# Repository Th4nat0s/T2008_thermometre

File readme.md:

Attiny84 Thermometer
=====================

Push code to attiny84
--------------------------------

### Attiny84
SPI Through BusPirate 
arduino framework 

Tips
----
`pio run` process/build project from the current directory  
`pio run -t upload` - upload firmware to a target  
`pio run -t clean` - clean project (remove compiled files)  
`pio run -t upload -e uno` upload only for arduino uno

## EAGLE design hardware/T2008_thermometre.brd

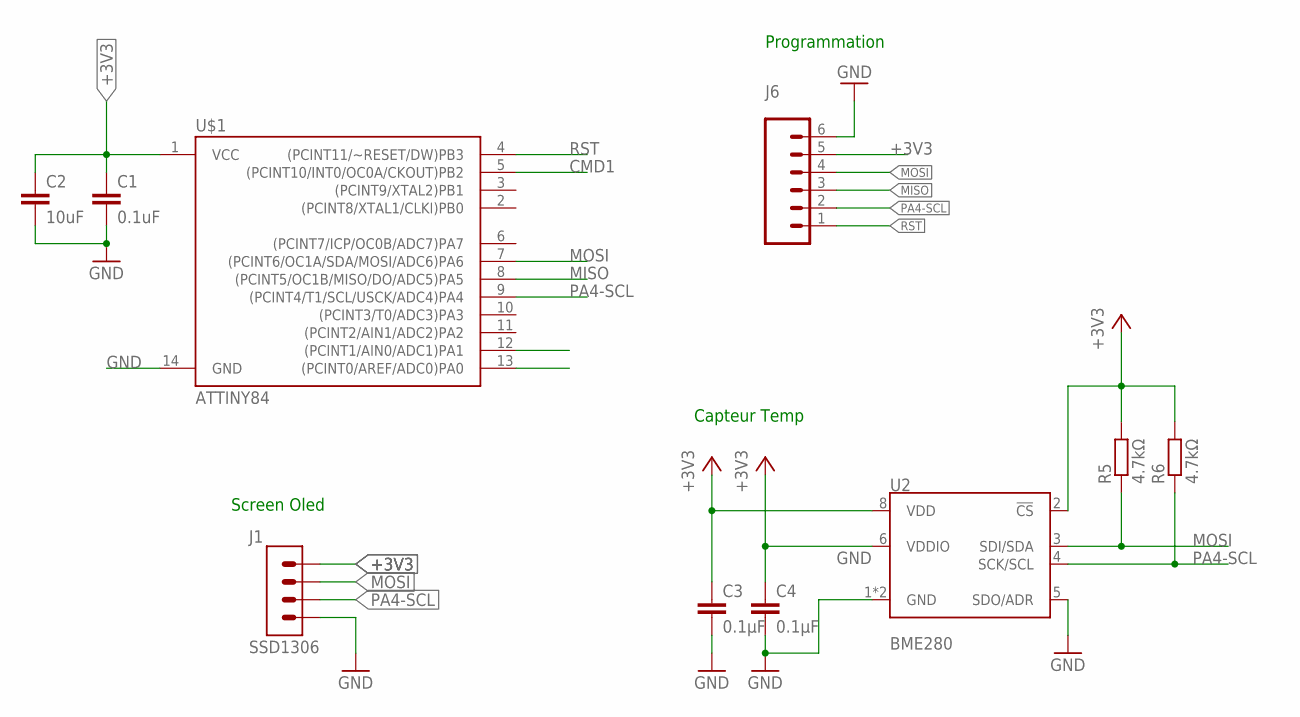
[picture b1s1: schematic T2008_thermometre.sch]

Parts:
C1: 0.1uF; C0603K
C2: 10uF; C0603K
C3, C4: 0.1µF; C0603K
J1: SSD1306; 62000411121
J6: CONN_06SMD_MALE; 1X06_SMD_MALE
R5, R6: 4.7kΩ; R0603
U2: BME280; LGA-8-2.5X2.5
U$1: ATTINY84; SO14

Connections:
+3V3: C1.1, C2.1, C3.1, C4.1, J1.1, J6.5, R5.2, R6.2, U2.2 (!CS), U2.6 (VDDIO), U2.8 (VDD), U$1.1 (VCC)
CMD1: U$1.5 ((PCINT10/INT0/OC0A/CKOUT)PB2)
GND: C1.2, C2.2, C3.2, C4.2, J1.4, J6.6, U2.1 (GND), U2.5 (SDO/ADR), U2.7 (GND), U$1.14 (GND)
MISO: J6.3, U$1.8 ((PCINT5/OC1B/MISO/DO/ADC5)PA5)
MOSI: J1.2, J6.4, R5.1, U2.3 (SDI/SDA), U$1.7 ((PCINT6/OC1A/SDA/MOSI/ADC6)PA6)
PA4-SCL: J1.3, J6.2, R6.1, U2.4 (SCK/SCL), U$1.9 ((PCINT4/T1/SCL/USCK/ADC4)PA4)
RST: J6.1, U$1.4 ((PCINT11/~RESET/DW)PB3)

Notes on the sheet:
Programmation
Capteur Temp
Screen Oled

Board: 2 copper layers, 10 parts (0 on the bottom side), 6 nets, no tracks yet.

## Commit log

2021-01-24 push code
2021-01-25 add hardware
2021-01-25 update lib
2021-01-25 cleanup code

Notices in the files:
parts and their libraries:
SparkFun-Connectors: Licensing: Creative Commons ShareAlike 4.0 International - https://creativecommons.org/licenses/by-sa/4.0
